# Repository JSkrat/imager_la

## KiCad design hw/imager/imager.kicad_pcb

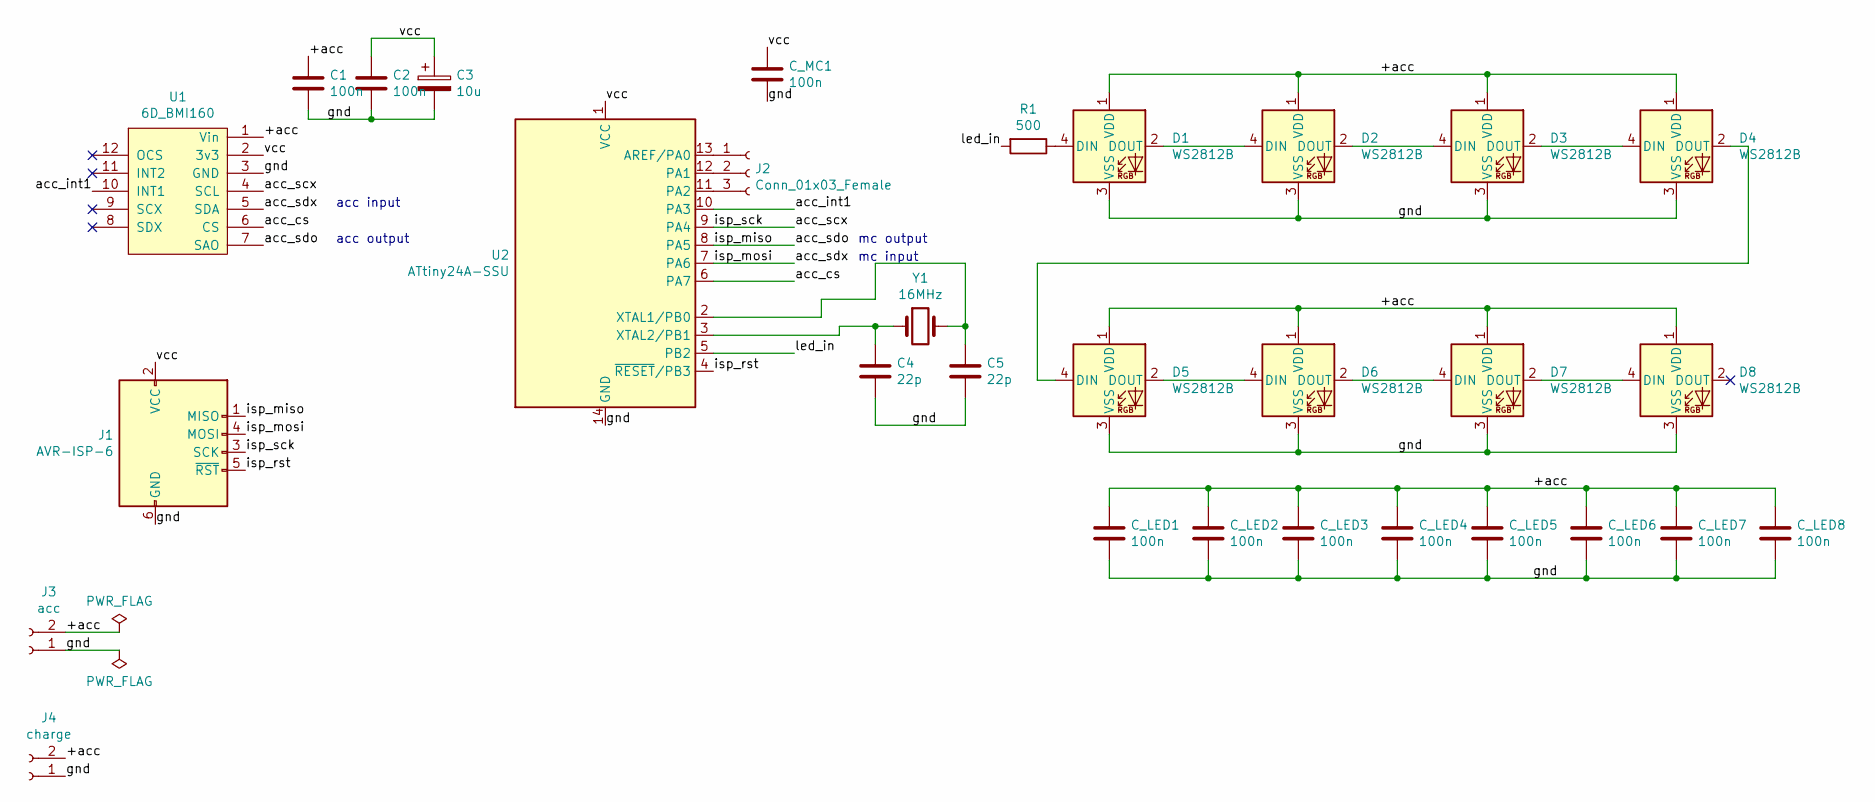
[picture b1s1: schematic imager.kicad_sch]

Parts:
C1, C2: 100n; C_0805_HandSoldering
C3: 10u; C_1206_HandSoldering
C4, C5: 22p; C_0805_HandSoldering
C_LED1, C_LED2, C_LED3, C_LED4, C_LED5, C_LED6, C_LED7, C_LED8: 100n; C_0805_HandSoldering
C_MC1: 100n; C_0805_HandSoldering
D1, D2, D3, D4, D5, D6, D7, D8: WS2812B; LED_WS2812B_PLCC4_5.0x5.0mm_P3.2mm
J1: AVR-ISP-6; AVR_ISP_TH_6
J2: Conn_01x03_Female; Pin_Header_Straight_1x03_Pitch2.54mm
J3: acc; Pin_Header_Straight_1x02_Pitch2.54mm
J4: charge; Pin_Header_Straight_1x02_Pitch2.54mm
R1: 500; R_0805_HandSoldering
U1: 6D_BMI160
U2: ATtiny24A-SSU; SOIC-14_3.9x8.7mm_P1.27mm
Y1: 16MHz; Crystal_HC18-U_Vertical

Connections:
/+acc: C1.1, C_LED1.1, C_LED2.1, C_LED3.1, C_LED4.1, C_LED5.1, C_LED6.1, C_LED7.1, C_LED8.1, D1.1 (VDD), D2.1 (VDD), D3.1 (VDD), D4.1 (VDD), D5.1 (VDD), D6.1 (VDD), D7.1 (VDD), D8.1 (VDD), J3.2, J4.2, U1.1 (Vin)
/acc_cs: U1.6 (CS), U2.6 (PA7)
/acc_int1: U1.10 (INT1), U2.10 (PA3)
/acc_scx: J1.3 (SCK), U1.4 (SCL), U2.9 (PA4)
/acc_sdo: J1.1 (MISO), U1.7 (SAO), U2.8 (PA5)
/acc_sdx: J1.4 (MOSI), U1.5 (SDA), U2.7 (PA6)
/gnd: C1.2, C2.2, C3.2, C4.2, C5.2, C_LED1.2, C_LED2.2, C_LED3.2, C_LED4.2, C_LED5.2, C_LED6.2, C_LED7.2, C_LED8.2, C_MC1.2, D1.3 (VSS), D2.3 (VSS), D3.3 (VSS), D4.3 (VSS), D5.3 (VSS), D6.3 (VSS), D7.3 (VSS), D8.3 (VSS), J1.6 (GND), J3.1, J4.1, U1.3 (GND), U2.14 (GND)
/isp_rst: J1.5 (~RST), U2.4 (~RESET/PB3)
/led_in: R1.2, U2.5 (PB2)
/vcc: C2.1, C3.1, C_MC1.1, J1.2 (VCC), U1.2 (3v3), U2.1 (VCC)
unnamed: C4.1, U2.3 (XTAL2/PB1), Y1.1
unnamed: C5.1, U2.2 (XTAL1/PB0), Y1.2
unnamed: D1.2 (DOUT), D2.4 (DIN)
unnamed: D1.4 (DIN), R1.1
unnamed: D2.2 (DOUT), D3.4 (DIN)
unnamed: D3.2 (DOUT), D4.4 (DIN)
unnamed: D4.2 (DOUT), D5.4 (DIN)
unnamed: D5.2 (DOUT), D6.4 (DIN)
unnamed: D6.2 (DOUT), D7.4 (DIN)
unnamed: D7.2 (DOUT), D8.4 (DIN)
unnamed: J2.1, U2.13 (AREF/PA0)
unnamed: J2.2, U2.12 (PA1)
unnamed: J2.3, U2.11 (PA2)

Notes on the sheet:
acc output
mc output
mc input
acc input

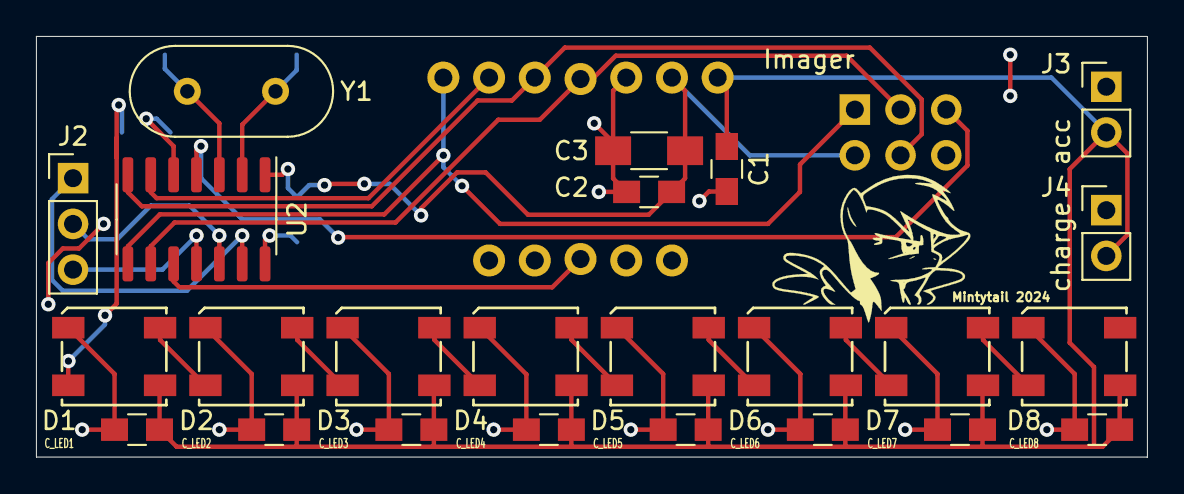
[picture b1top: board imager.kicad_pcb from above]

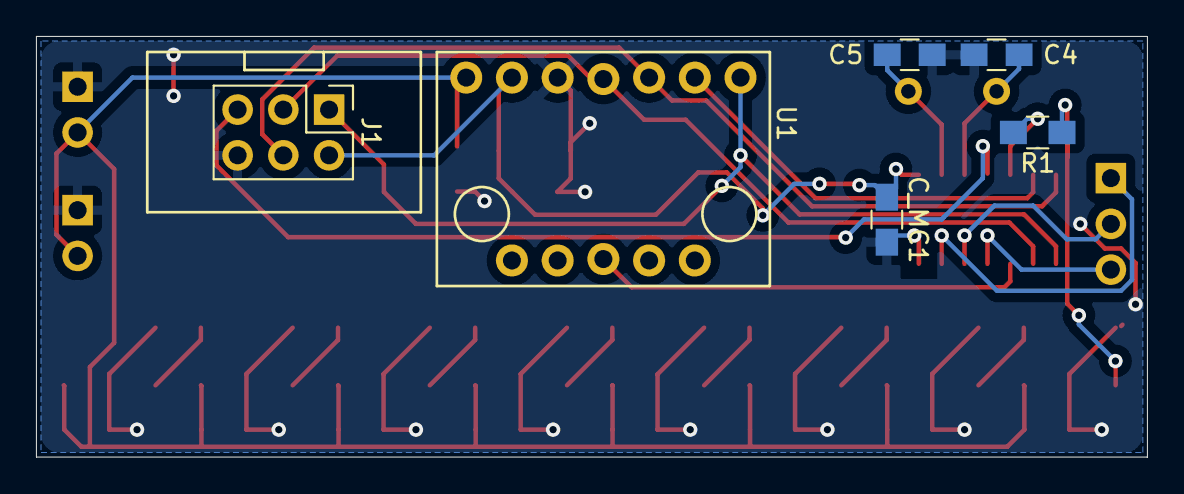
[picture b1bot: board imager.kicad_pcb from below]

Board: 2 copper layers, 61.7 x 23.4 mm, 30 parts (6 on the bottom side), 23 nets.

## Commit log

2024-02-21 add hardware
2024-02-21 add empty firmware add LED module and driver
2024-02-21 fw.led: remove irrelevant lines
2024-02-23 fw: add code for accelerometer spi communication, read, write registers low level
2024-03-16 fw: accelerometer SPI communication
2024-03-16 hw: added spi input/output markings (there's an error in the PCB)
2024-07-12 fw: add test image (raw accelerometer readings)
